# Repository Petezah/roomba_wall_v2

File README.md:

# roomba_wall_v2

An AVR device, based on ATTiny85, to transmit a virtual wall signal for an iRobot Roomba

## Folder layout

* /firmware
  * Source for the ATTiny85 firmware
* /hardware
  * Files describing the board layout, etc
* /christmas_tree_barrier
  * Files describing the board layout for the Christmas tree barrier variation

## Building

### Prerequisites for "happy path":

* Raspberry Pi configured with BCM SPI enabled
* AVR-GCC installed
  *  Easiest way to get this is 'sudo apt-get install arduino'
* Either:
  * A 6-position, dual-row IDC cable (recommended)
  * Or jumpers to wire SPI bus of Raspberry Pi to the ISP pads on the finished board

### Steps

#### hardware

* Order a board based on the files in https://github.com/Petezah/roomba_wall_v2/tree/master/hardware
  * Alternately, order one directly from OSH Park here: https://oshpark.com/shared_projects/yCviCn7Z
* Purchase parts from [Mouser electronics](http://mouser.com) using the current BOM
  * Use the ones with "mouser" in their filenames
* Assemble the board--parts are all marked on the silkscreen
  * NB: The ISP header should not be soldered to the board--merely insert the header pins into the IDC cable and wedge the pins into the vias during programming

#### firmware

There are two methods to wire the board for programming:

* *Recommended way*:
  *  Order my Raspberry Pi ISP board here: https://oshpark.com/shared_projects/iYtnPahC
  *  Assemble, and use an IDC cable as described above

* Alternate way: 
  * Hook up the ISP pins on the assembled board to your Raspberry PI as follows:
    * ISP Pin 1 --> Raspberry Pi Pin 21 (MISO)
    * ISP Pin 2 --> Raspberry Pi Pin 17 (3.3V)
    * ISP Pin 3 --> Raspberry Pi Pin 23 (SCK)
    * ISP Pin 4 --> Raspberry Pi Pin 19 (MOSI)
    * ISP Pin 5 --> Raspberry Pi Pin 15 (GPIO22)
    * ISP Pin 6 --> Raspberry Pi Pin 25 (GND)

Once wiring is accomplished:
* Execute the following on the Raspberry Pi command line
  * cd firmware
  * make fuse
  * make install

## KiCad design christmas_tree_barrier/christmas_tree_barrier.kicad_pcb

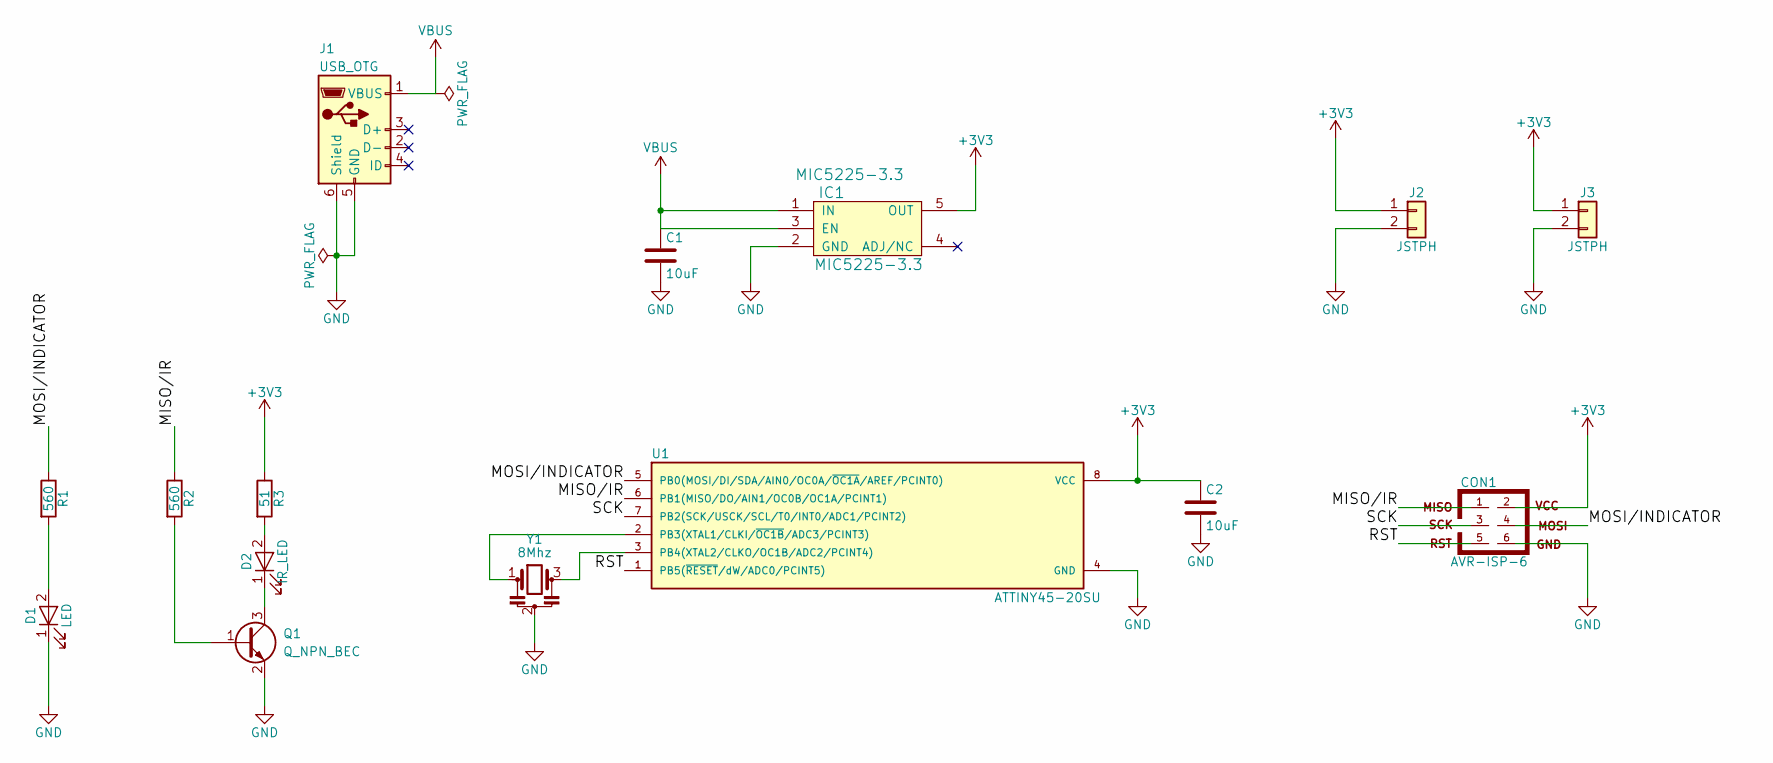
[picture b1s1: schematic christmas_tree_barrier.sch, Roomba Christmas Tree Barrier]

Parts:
C1, C2: 10uF; C_1206
CON1: AVR-ISP-6; Pin_Header_Straight_2x03_Pitch2.54mm
D1: LED; LED_1206
D2: IR_LED; LED_0603_HandSoldering
IC1: MIC5225-3.3; SOT-23-5_HandSoldering; mfr# MIC5225-3.3
J1: USB_OTG; USB_Micro-B_10103594-0001LF
J2, J3: JSTPH; JST_PH_B2B-PH-SM4-TB_02x2.00mm_Straight
Q1: Q_NPN_BEC; SOT-23_Handsoldering
R1, R2: 560; R_1206
R3: 51; R_1206
U1: ATTINY45-20SU; SOIC-8_5.35x5.40mm_Pitch1.27mm
Y1: 8Mhz; Resonator_SMD_muRata_CSTCE_G-3pin_3.0x0.7mm

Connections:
+3V3: C2.1, CON1.2, IC1.5 (OUT), J2.1, J3.1, R3.1, U1.8 (VCC)
/MISO/IR: CON1.1, R2.1, U1.6 (PB1(MISO/DO/AIN1/OC0B/OC1A/PCINT1))
/MOSI/INDICATOR: CON1.4, R1.1, U1.5 (PB0(MOSI/DI/SDA/AIN0/OC0A/~OC1A~/AREF/P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)
/RST: CON1.5, U1.1 (PB5(~RESET~/dW/ADC0/PCINT5))
/SCK: CON1.3, U1.7 (PB2(SCK/USCK/SCL/T0/INT0/ADC1/PCINT2))
GND: C1.2, C2.2, CON1.6, D1.1 (K), IC1.2 (GND), J1.5 (GND), J1.6 (Shield), J2.2, J3.2, Q1.2 (E), U1.4 (GND), Y1.2
unnamed: D1.2 (A), R1.2
unnamed: D2.1 (K), Q1.3 (C)
unnamed: D2.2 (A), R3.2
unnamed: Q1.1 (B), R2.2
unnamed: U1.2 (PB3(XTAL1/CLKI/~OC1B~/ADC3/PCINT3)), Y1.1
unnamed: U1.3 (PB4(XTAL2/CLKO/OC1B/ADC2/PCINT4)), Y1.3
VBUS: C1.1, IC1.1 (IN), IC1.3 (EN), J1.1 (VBUS)

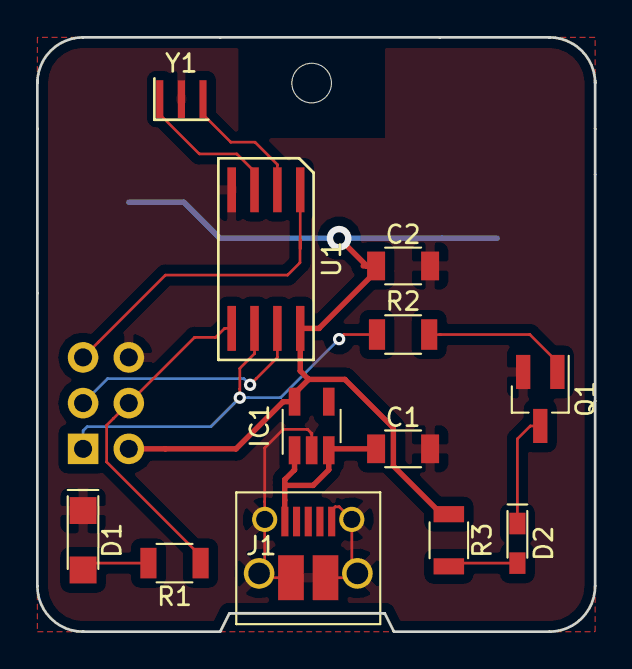
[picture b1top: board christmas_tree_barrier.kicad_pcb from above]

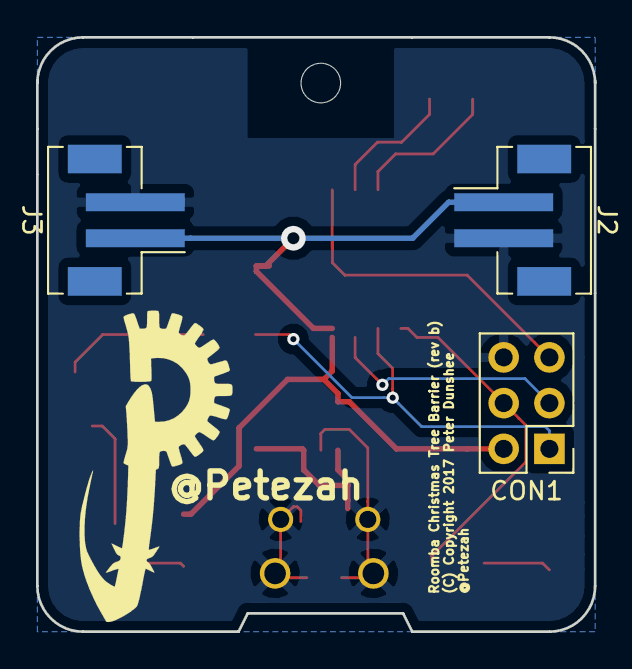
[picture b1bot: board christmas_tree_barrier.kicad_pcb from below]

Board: 2 copper layers, 31.0 x 33.0 mm, 15 parts (3 on the bottom side), 13 nets.

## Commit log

2016-05-12 Starting with v1 of the roomba wall project
2016-05-12 Reworked project for bare ATTiny85 * Moved 3rd party roomba send logic into its own file * Integrated just the portions of the IRRemote library that we need * Integrated our one Arduino dependency, w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
2016-05-13 Trying to switch our clock over to timer 1 to free up timer 0 exclusively for pwm
2016-05-13 Simplified by eliminating the clock timing required by the wiring delay functions and instead use a hand-tuned delay function specifically for 8Mhz ATTiny85 from the TV-B-Gone project. Also inspired 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
2016-05-15 Made a layout image of the prototype for reference. Moved hardware and firmware files into separate directories.
2016-05-16 Update README.md
    Added build steps, etc.
2016-05-18 Rev A of schematic and pcb layout
2016-05-18 BOM in CSV format
2016-05-23 Exported more useful BOM from Mouser
2016-06-05 Photo of the finished product
2016-06-05 Update readme with current instructions
2016-06-05 Fixed image link
2016-06-15 Doubled the IR transmit delay This is an experiment, attempting to extend the battery life of the device.
2016-06-15 Changed the timing to improve battery life again It now transmits once per second instead of once per .02 seconds. Testing the firmware with the device, it still stops the roomba. Battery life should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
2016-08-22 PCB layout, rev B 1/3 smaller, with mounting holes and cutout for the battery holder
2016-08-22 Update schematic printout
2016-09-04 Rev C and D boards C: ATTiny85/45 in SOIC package D: ATTiny45 in TSSOP package
2016-09-10 Reorganize project and update BOM
2016-09-10 Updated the readme
2016-09-21 Fixed some bits that never got updated Some instructions changed with Rev B; I missed some steps in prerequisites
2016-09-21 Updated image with picture of rev B board
2016-10-30 Rev E board SOIC ATTiny 1206 indicator LED 0603 IR LED
    Larger uC to make assembly easier than the SSOP. SMD LEDs to make the board more durable to life in the hallway.
2017-11-26 Print out size during buildwq
2017-11-26 Latest changes to rev E Not sure what's in here; they were made a while ago and just weren't committed. This is possibly the fix to the unconnected GND on the MCU.
2017-11-26 Starting Christmas tree barrier project
2017-11-27 Finished new schematic; started pcb layout
2017-11-28 Working on new pcb
2017-11-28 Place parts nicely
2017-11-28 Mostly finalize placement and outline
2017-11-29 Finished layout and routing Also just a bit of silkscreen
2017-12-01 Archive symbols and footprints
2017-12-01 Ignore KiCAD backup files
2017-12-04 Fix transistor on schematic Accidentally had a PNP instead of an NPN; doesn't change the PCB layout, I just made the mistake on the schematic.
2018-01-03 Fix footprints SOIC-8 was wrong--body was too narrow and pads too short LEDs were unclear--cathode indicator was on top of solder mask area
    Also plotted gerbers
2018-02-21 Latest PCB work
2018-02-24 Tweaks for Christmas tree barrier
2018-02-24 Latest gerber plots
2020-12-12 Rev b of Christmas Tree Barrier
    SOIC footprint is now fixed (wider pads)

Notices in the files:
christmas_tree_barrier/christmas_tree_barrier.kicad_pcb:
(C) 2017 Peter Dunshee
(C) Copyright 2017 Peter Dunshee
